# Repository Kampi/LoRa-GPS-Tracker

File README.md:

# LoRa-GPS-Tracker

## Table of Contents

- [LoRa-GPS-Tracker](#lora-gps-tracker)
  - [Table of Contents](#table-of-contents)
  - [About](#about)
  - [Directory structure](#directory-structure)
  - [Purchasing](#purchasing)
  - [Programming](#programming)
  - [Maintainer](#maintainer)

## About

This is a project for a LoRa based APRS GPS tracker.

## Directory structure

- `docs`: All kinds of project documentation
- `firmware`: The firmware project for the tracker
- `project`: KiCad project for the PCB
- `testing`: 

## Purchasing

Please open `LoRa-GPS-Tracker-navigate.html` and use the files listed under `purchasing` for ordering a PCB.

## Programming

1. Download and install [STM32CubeProgrammer](https://www.st.com/en/development-tools/stm32cubeprog.html)
2. Close the `PROG` jumper on the PCB
3. Connect the board via USB to your PC
4. Open `Memory & File editing` in `STM32CubeProgrammer`
5. Select `UART`, the target COM port and `Read Unprotect (MCU)`
6. Click `Connect` and wait for a connection
7. Open `Erase & Programming` and click `Browse`

## Maintainer

- [Daniel Kampert](mailto:daniel.kameprt@kampis-elektroecke.de)

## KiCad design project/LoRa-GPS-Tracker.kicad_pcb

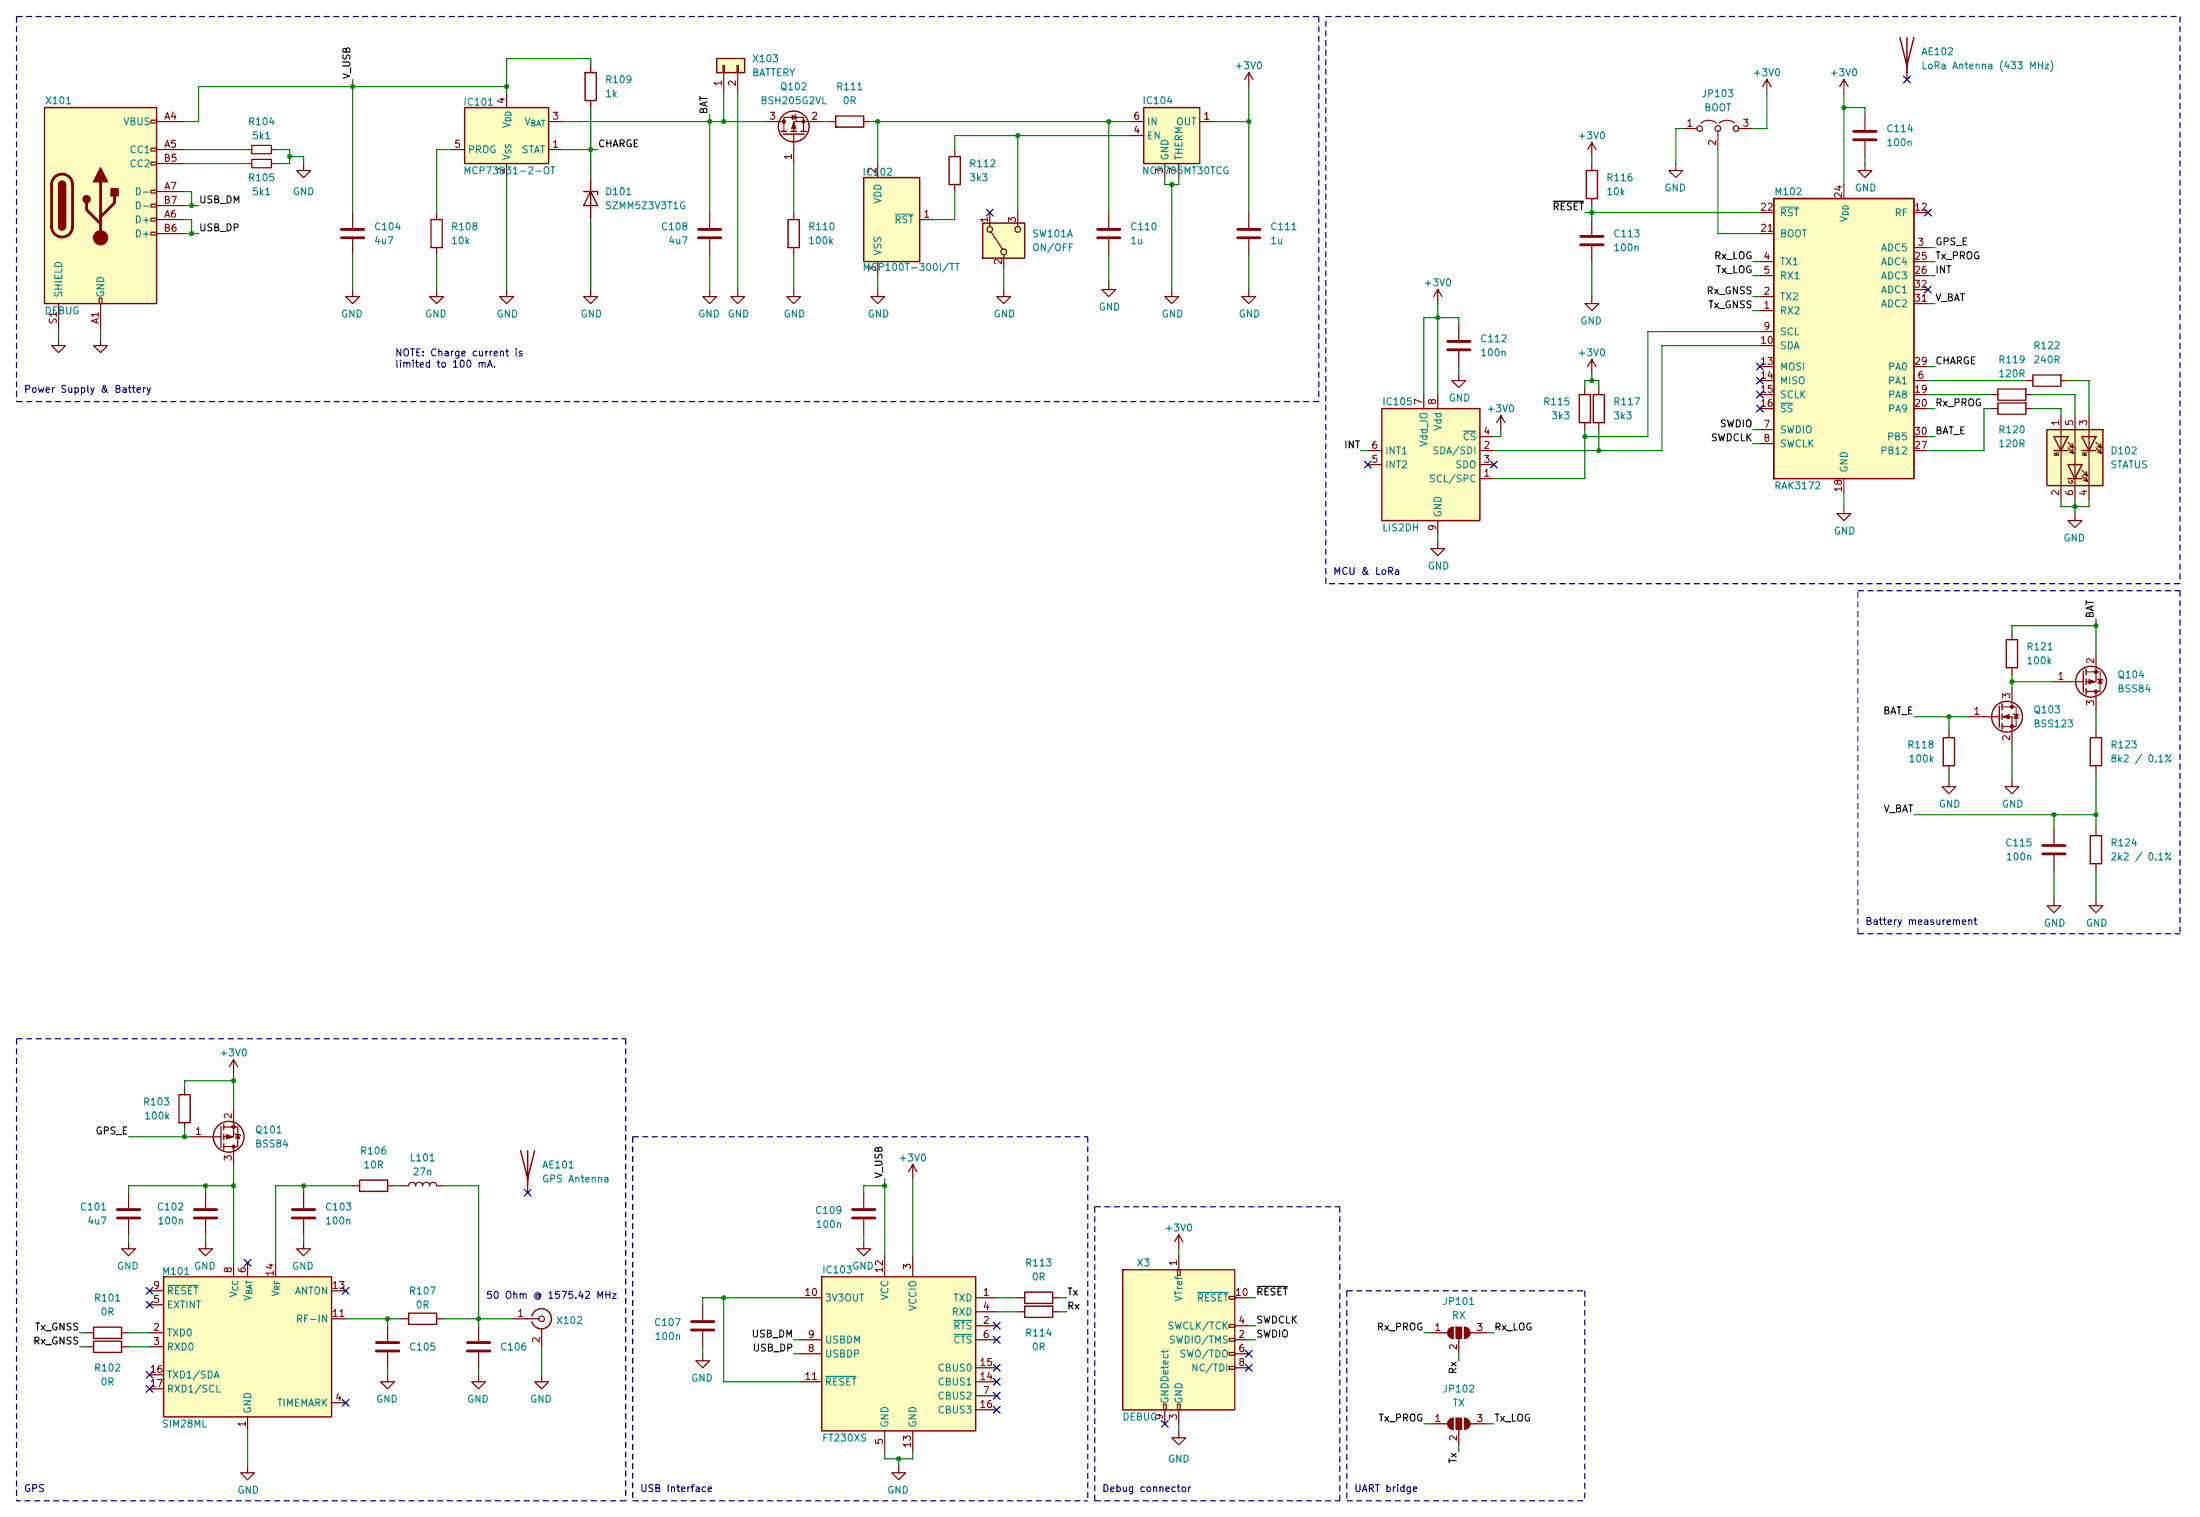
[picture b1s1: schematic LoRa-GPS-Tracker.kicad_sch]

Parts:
AE101: GPS Antenna
AE102: LoRa Antenna (433 MHz)
C101, C104, C108: 4u7; C_0402_1005Metric_Pad0.74x0.62mm_HandSolder
C102, C103, C107, C109, C112, C113, C114, C115: 100n; C_0402_1005Metric_Pad0.74x0.62mm_HandSolder
C105, C106: C_0402_1005Metric_Pad0.74x0.62mm_HandSolder
C110, C111: 1u; C_0402_1005Metric_Pad0.74x0.62mm_HandSolder
D101: SZMM5Z3V3T1G; D_SOD-523
D102: STATUS; QLS6B-FKW-CNSNSF043
IC101: MCP73831-2-OT; SOT-23-5
IC102: MCP100T-300I/TT; SOT-23
IC103: FT230XS; SSOP-16_3.9x4.9mm_P0.635mm
IC104: NCP705MT30TCG; WDFN-6
IC105: LIS2DH; LGA-14_2x2mm_P0.35mm_LayoutBorder3x4y
JP101: RX; SolderJumper-3_P1.3mm_Open_RoundedPad1.0x1.5mm_NumberLabels
JP102: TX; SolderJumper-3_P1.3mm_Open_RoundedPad1.0x1.5mm_NumberLabels
JP103: BOOT; SolderJumper-3_P1.3mm_Open_RoundedPad1.0x1.5mm_NumberLabels
L101: 27n; L_0402_1005Metric_Pad0.77x0.64mm_HandSolder
M101: SIM28ML
M102: RAK3172
Q101, Q104: BSS84; SOT-23
Q102: BSH205G2VL; SOT-23
Q103: BSS123; SOT-23
R101, R102, R107, R113, R114: 0R; R_0402_1005Metric_Pad0.72x0.64mm_HandSolder
R103, R110, R118, R121: 100k; R_0402_1005Metric_Pad0.72x0.64mm_HandSolder
R104, R105: 5k1; R_0402_1005Metric_Pad0.72x0.64mm_HandSolder
R106: 10R; R_0402_1005Metric_Pad0.72x0.64mm_HandSolder
R108, R116: 10k; R_0402_1005Metric_Pad0.72x0.64mm_HandSolder
R109: 1k; R_0402_1005Metric_Pad0.72x0.64mm_HandSolder
R111: 0R; R_0805_2012Metric_Pad1.20x1.40mm_HandSolder
R112, R115, R117: 3k3; R_0402_1005Metric_Pad0.72x0.64mm_HandSolder
R119, R120: 120R; R_0402_1005Metric_Pad0.72x0.64mm_HandSolder
R122: 240R; R_0402_1005Metric_Pad0.72x0.64mm_HandSolder
R123: 8k2 / 0.1%; R_0402_1005Metric_Pad0.72x0.64mm_HandSolder
R124: 2k2 / 0.1%; R_0402_1005Metric_Pad0.72x0.64mm_HandSolder
SW101: ON/OFF; SW_SPDT_PCM12
X3: DEBUG; SHF-105-01-L-D-SM-TR
X101: DEBUG; USB_C_Receptacle_GCT_USB4105-xx-A_16P_TopMnt_Horizontal
X102: Conn_Coaxial; 73412-0110
X103: BATTERY; 78171-0002

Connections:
+3V0: C111.1, C112.1, C114.1, IC103.3 (VCCIO), IC104.1 (OUT), IC105.4 (~CS), IC105.7 (Vdd_IO), IC105.8 (Vdd), JP103.3 (B), M102.24 (VDD), Q101.2 (S), R103.1, R115.1, R116.1, R117.1; also elsewhere on the board
/BAT: C108.1, IC101.3 (V_{BAT}), Q102.3 (D), Q104.2 (S), R121.1, X103.1
/BAT_E: M102.30 (PB5), Q103.1 (G), R118.1
/CHARGE: D101.1 (K), IC101.1 (STAT), M102.29 (PA0), R109.1
/GPS_E: M102.3 (ADC5), Q101.1 (G), R103.2
/INT: IC105.6 (INT1), M102.26 (ADC3)
/Rx: JP101.2 (C), R114.2
/Rx_GNSS: M102.2 (TX2), R102.1
/Rx_LOG: JP101.3 (B), M102.4 (TX1)
/Rx_PROG: JP101.1 (A), M102.20 (PA9)
/SWDCLK: M102.8 (SWCLK); also elsewhere on the board
/SWDIO: M102.7 (SWDIO); also elsewhere on the board
/Tx: JP102.2 (C), R113.1
/Tx_GNSS: M102.1 (RX2), R101.1
/Tx_LOG: JP102.3 (B), M102.5 (RX1)
/Tx_PROG: JP102.1 (A), M102.25 (ADC4)
/USB_DM: IC103.9 (USBDM), X101.A7 (D-), X101.B7 (D-)
/USB_DP: IC103.8 (USBDP), X101.A6 (D+), X101.B6 (D+)
/V_BAT: C115.1, M102.31 (ADC1), R123.2, R124.1
/V_USB: C104.1, C109.1, IC101.4 (V_{DD}), IC103.12 (VCC), R109.2, X101.A4 (VBUS), X101.A9 (VBUS), X101.B4 (VBUS), X101.B9 (VBUS)
/~RESET: C113.1, M102.22 (~RST), R116.2; also elsewhere on the board
GND: C101.2, C102.2, C103.2, C104.2, C105.2, C106.2, C107.2, C108.2, C109.2, C110.2, C111.2, C112.2, C113.2, C114.2, C115.2, D101.2 (A), D102.2 (KB), D102.4 (KR), D102.6 (KR), IC101.2 (V_{SS}), IC102.3 (VSS), IC103.5 (GND), IC103.13 (GND), IC104.3 (GND), IC104.7 (THERM), IC105.9 (GND), IC105.10 (GND), IC105.11 (GND), IC105.12 (GND), IC105.13 (GND), IC105.14 (GND), JP103.1 (A), M101.1 (GND), M101.10 (GND), M101.12 (GND), M102.11 (VSS), M102.17 (VSS), M102.18 (VSS), M102.23 (VSS), M102.28 (VSS), Q103.2 (S), R104.2, R105.1, R108.2, R110.2, R118.2, R124.2, SW101.2 (B), X101.A1 (GND), X101.A12 (GND), X101.B1 (GND), X101.B12 (GND), X101.S1 (SHIELD), X102.2 (Ext), X103.2; also elsewhere on the board
unnamed: D102.1 (AB), R120.2
unnamed: D102.5 (AG), R119.2
unnamed: D102.3 (AR), R122.2
unnamed: IC101.5 (PROG), R108.1
unnamed: C110.1, IC102.2 (VDD), IC104.6 (IN), R111.1
unnamed: IC102.1 (~RST), R112.2
unnamed: C107.1, IC103.10 (3V3OUT), IC103.11 (~RESET)
unnamed: IC103.4 (RXD), R114.1
unnamed: IC103.1 (TXD), R113.2
unnamed: IC104.4 (EN), R112.1, SW101.3 (C)
unnamed: IC105.1 (SCL/SPC), M102.9 (SCL), R115.2
unnamed: IC105.2 (SDA/SDI), M102.10 (SDA), R117.2
unnamed: JP103.2 (C), M102.21 (BOOT)
unnamed: L101.1, R106.2
unnamed: C105.1, M101.11 (RF_IN), R107.1
unnamed: M101.3 (RXD0), R102.2
unnamed: M101.2 (TXD0), R101.2
unnamed: C101.1, C102.1, M101.8 (VCC), Q101.3 (D)
unnamed: C103.1, M101.14 (VCC_RF), R106.1
unnamed: M102.6 (PA1), R122.1
unnamed: M102.19 (PA8), R119.1
unnamed: M102.27 (PB12), R120.1
unnamed: Q102.1 (G), R110.1
unnamed: Q102.2 (S), R111.2
unnamed: Q103.3 (D), Q104.1 (G), R121.2
unnamed: Q104.3 (D), R123.1
unnamed: R104.1, X101.A5 (CC1)
unnamed: R105.2, X101.B5 (CC2)
unnamed: C106.1, L101.2, R107.2, X102.1 (In)

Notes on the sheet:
Debug connector
GPS
USB Interface
UART bridge
50 Ohm @ 1575.42 MHz
Battery measurement
Power Supply & Battery
NOTE: Charge current is limited to 100 mA.
MCU & LoRa

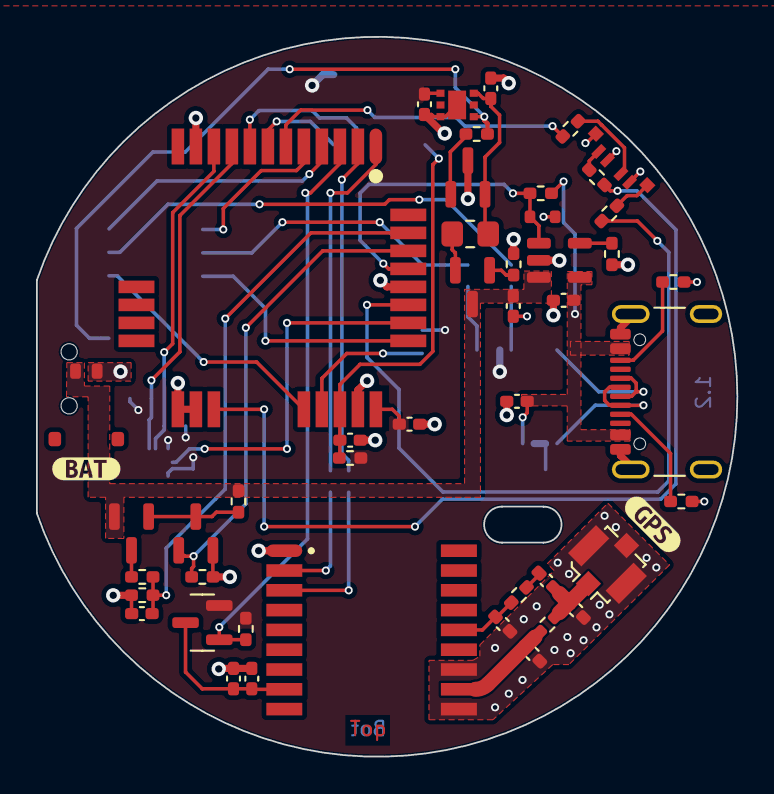
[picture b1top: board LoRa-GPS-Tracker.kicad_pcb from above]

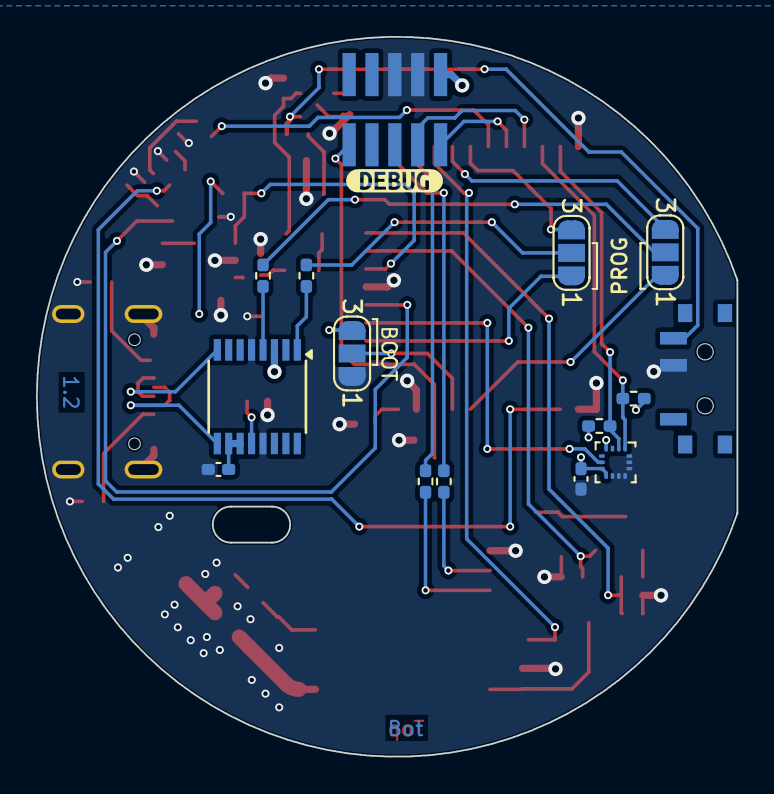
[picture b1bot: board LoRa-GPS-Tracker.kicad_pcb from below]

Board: 2 copper layers, 38.9 x 40.0 mm, 64 parts (16 on the bottom side), 51 nets.

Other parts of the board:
X104: DEBUG; SHF-105-01-L-D-SM-TR
kibuzzard-65A187C4: G***; kibuzzard-65A187C4
kibuzzard-65A18804: G***; kibuzzard-65A18804
kibuzzard-66008FCD: G***; kibuzzard-66008FCD

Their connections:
+3V0: X104.1 (VTref); also elsewhere on the board
/SWDCLK: X104.4 (SWCLK/TCK); also elsewhere on the board
/SWDIO: X104.2 (SWDIO/TMS); also elsewhere on the board
/~RESET: X104.10 (~RESET); also elsewhere on the board
GND: X104.3 (GND), X104.5 (GND); also elsewhere on the board

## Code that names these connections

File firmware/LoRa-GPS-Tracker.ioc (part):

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Mcu.Name=STM32WLE5CCUx
Mcu.Package=UFQFPN48
Mcu.UserName=STM32WLE5CCUx
PA0.GPIOParameters=GPIO_PuPd,GPIO_Label
PA0.GPIO_Label=CHARGE
PA0.GPIO_PuPd=GPIO_PULLDOWN
PA0.Signal=GPIO_Input
PA1.GPIOParameters=GPIO_Label
PA1.GPIO_Label=LED3
PA1.Signal=GPIO_Output
PA10.Mode=I2C
PA10.Signal=I2C1_SDA
PA13.Mode=Serial_Wire
PA13.Signal=DEBUG_JTMS-SWDIO
PA14.Mode=Serial_Wire
PA14.Signal=DEBUG_JTCK-SWCLK
PA15.GPIOParameters=GPIO_PuPd,GPIO_Label
PA15.GPIO_Label=GPS_E
PA15.GPIO_PuPd=GPIO_PULLUP
PA15.Signal=GPIO_Output
PA2.GPIOParameters=GPIO_Label
PA2.GPIO_Label=GPS_TX
PA2.Mode=Asynchronous
PA2.Signal=LPUART1_TX
PA3.GPIOParameters=GPIO_Label
PA3.GPIO_Label=GPS_RX
PA3.Mode=Asynchronous
PA3.Signal=LPUART1_RX
PA8.GPIOParameters=GPIO_Label
PA8.GPIO_Label=LED2
PA8.Signal=GPIO_Output
PA9.Mode=I2C
PA9.Signal=I2C1_SCL
PB12.GPIOParameters=GPIO_Label
PB12.GPIO_Label=LED1
PB12.Signal=GPIO_Output
PB2.GPIOParameters=GPIO_PuPd,GPIO_Label
PB2.GPIO_Label=INT
PB2.GPIO_PuPd=GPIO_NOPULL
PB2.Signal=GPIO_Input
PB3.GPIOParameters=GPIO_Label
PB3.GPIO_Label=V_BAT
PB3.Mode=IN2
PB3.Signal=ADC_IN2
PB5.GPIOParameters=GPIO_PuPd,GPIO_Label
PB5.GPIO_Label=BAT_E
PB5.GPIO_PuPd=GPIO_PULLDOWN
PB5.Signal=GPIO_Output
PB6.GPIOParameters=GPIO_Label
PB6.GPIO_Label=SERIAL_TX
PB6.Mode=Asynchronous
PB6.Signal=USART1_TX
PB7.GPIOParameters=GPIO_Label
PB7.GPIO_Label=SERIAL_RX
PB7.Mode=Asynchronous
PB7.Signal=USART1_RX
PC14-OSC32_IN.Mode=LSE-External-Oscillator
PC14-OSC32_IN.Signal=RCC_OSC32_IN
PC15-OSC32_OUT.Mode=LSE-External-Oscillator
PC15-OSC32_OUT.Signal=RCC_OSC32_OUT
RCC.HSE_VALUE=8000000
RCC.SYSCLKFreq_VALUE=48000000
board=NUCLEO-WL55JC1

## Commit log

2024-01-05 Initialize repository
2024-01-06 Add KiCad project
2024-01-07 Version 1
    PCB:
    - Update build.yaml
    - Add PCB variant for KiBot
2024-01-07 Add LoRa APRS iGate project for 868 MHz
2024-01-07 Add initial APRS demo for Nucleo board
2024-01-07 Apply gitignore
2024-01-07 Version 1.0
    - Add UART GPS parser
    - SubGHz PHY is now using the coordinates from GPS
2024-01-11 Version 1.0
    Electronics:
    - Add jumper for current measurement
    - Add jumper to set the RAK module into bootloader mode
    - Add capacitor for battery measurement
    Testing Firmware:
    - Add UART GPS parser
2024-01-12 Working on version 1:
    Hardware:
    - Fix empty ZIP files in KiBot template
    - Fix missing drill files in KiBot template
    - Add optional SWD connector for debugging
    - Add minimal variant without UART console and SWD connector
    Nucleo Demo:
2024-01-13 Update build.yml
    Add variants to build.yml
2024-01-14 Working on version 1
    Hardware:
    - Finalize PCB
    - Replace expensive components with cheaper ones
    - Add GPS antenna
2024-02-07 Working on version 1
    Hardware:
    - Finalize PCB
    - Replace expensive components with cheaper ones
    - Add GPS antenna
    Firmware Testing:
    - Add GPS configuration
2024-02-09 Add image from CI/CD action
2024-02-11 Hardware: - Add RESET line for SWD interface - Replace micro USB with USB C
    Software:
    - Add firmware for LoRa-GPS-Tracker PCB
2024-04-19 - Upgrade KiBot to support KiCad 8
2024-04-28 - Fix wrong pinout for UART bootloader - Update documentation for bootloader
2024-10-05 Fix GPS code for Nucleo
2024-10-05 Update CI/CD workflow
2024-10-05 Improving testing firmware
2024-10-05 Add missing part numbers and datasheets
2024-10-06 Make it possible to power cycle the GPS module
2024-10-06 Add I2C accelerometer
2024-10-26 Fix wrong package for CC resistors
2024-10-27 Fix wrong footprint for status LED

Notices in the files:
README.md:
License: GPL 3.0
